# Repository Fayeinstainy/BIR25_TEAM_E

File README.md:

# Smart Swarmica - A Swarm Ant Robots Project
## Overview
This project is part of a biologically-inspired swarm robot system, where multiple robots cooperate to perform tasks such as locating a wireless charger and coordinating actions using IR signals.
All circuities were **initially developed and tested on a Raspberry Pi Pico**, and later **finalized on a custom PCB using RP2035 microcontroller chip** for integration into the final robot design.
The video for the whole development process and final demonstration can be found via this link: https://www.youtube.com/watch?v=agExd-AKbOk 

## Hardware Component 

- **IR LED**: IR333
- **IR Receiver**: TSOP38238
- **Microcontroller**: RP2350-based Raspberry Pi Pico 2W
  
- **Other**: Resistors, Transistors (for LED driving), 38kHz signal source (via PWM)

## System Architecture

## Power System Architecture (Normal Operation Mode)

## Software Architecture

## Motor Control
## Navigation
## Infrared Communication
- Uses **modulated IR signals** at 38kHz for one-way signaling between robots.
- Encodes simple messages (e.g. "Relative location is (4, 12)", "Stop Moving").
- Receiver uses TSOP382 to detect incoming signals reliably even in ambient light.

### How it works:
1. IR LED emits 38kHz modulated pulses.
2. TSOP382 detects signal and triggers logic in firmware.
3. Signal interpreted as communication or wall proximity.

## PCB Design
Designed using kiCAD 9.0, project files, schematic and PCB pdfs under bio_robots/ folder, featuring the following features:
- Populated: Common anode RGB LED, 3-pairs of IR transmitters and receivers, full bridge rectifier, parallel chargers for the supercapacitors, OR controller.
- Unpopulated: ICM-20948, 1.8V regulator, level shifters, bypass strategy (U12, D10-D13)

## Obstacle Avoidance
- Based on detecting reflection of IR signal from nearby obstacles.
- If TSOP382 receives the robot’s own IR pulses reflected from a wall, it triggers a "wall detected" event.
##  WI-FI Programming Mode

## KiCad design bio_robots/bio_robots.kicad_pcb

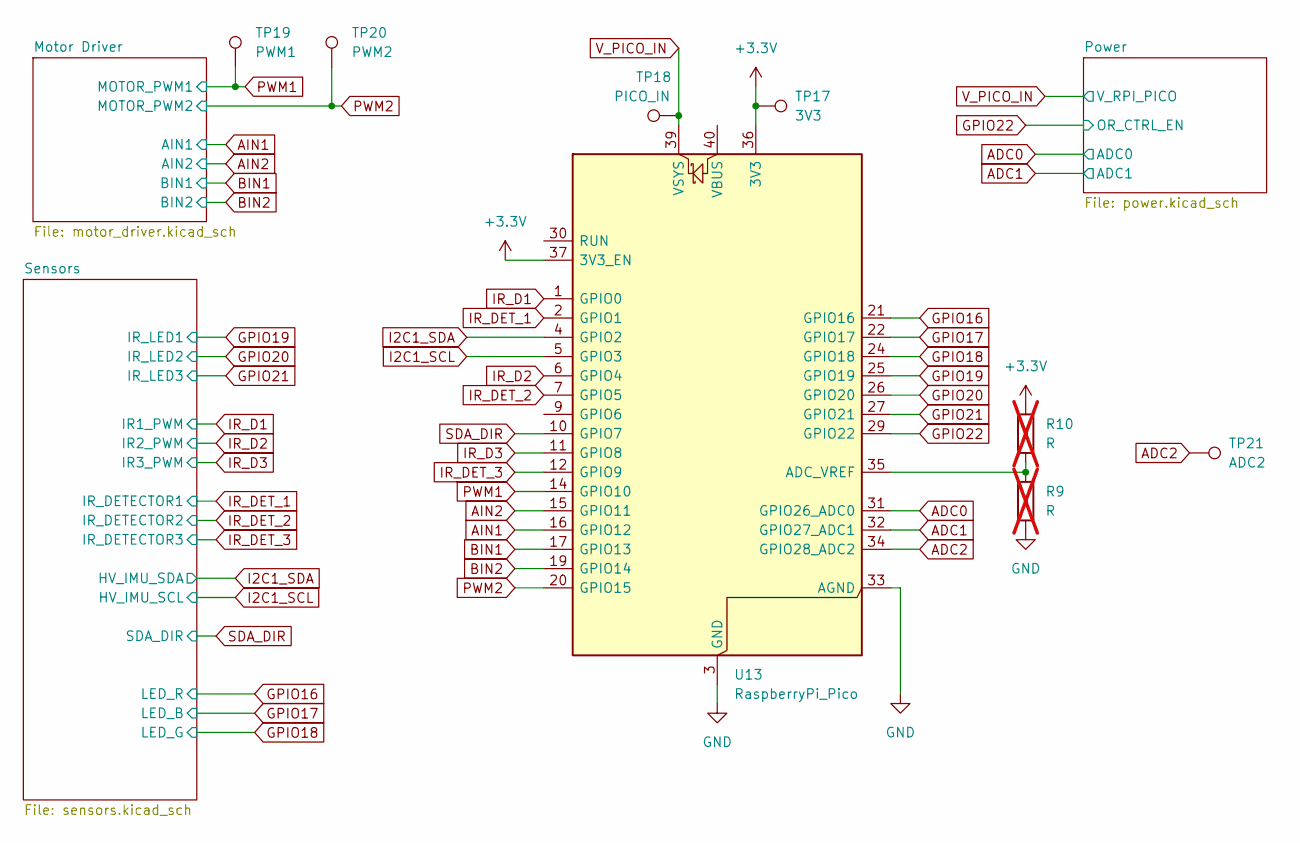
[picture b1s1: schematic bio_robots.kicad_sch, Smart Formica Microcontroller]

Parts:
R9, R10: R; R_0603_1608Metric_Pad0.98x0.95mm_HandSolder; not fitted
TP17: 3V3; TestPoint_Pad_D1.0mm
TP18: PICO_IN; TestPoint_Pad_D1.0mm
TP19: PWM1; TestPoint_Pad_D1.0mm
TP20: PWM2; TestPoint_Pad_D1.0mm
TP21: ADC2; TestPoint_Pad_D1.0mm
U13: RaspberryPi_Pico; mod_RaspberryPi_Pico_Common_THT

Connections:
ADC0: U13.31 (GPIO26_ADC0); also elsewhere on the board
ADC1: U13.32 (GPIO27_ADC1); also elsewhere on the board
ADC2: TP21.1, U13.34 (GPIO28_ADC2)
AIN1: U13.16 (GPIO12); also elsewhere on the board
AIN2: U13.15 (GPIO11); also elsewhere on the board
BIN1: U13.17 (GPIO13); also elsewhere on the board
BIN2: U13.19 (GPIO14); also elsewhere on the board
GND: R9.2, U13.3 (GND), U13.8 (GND), U13.13 (GND), U13.18 (GND), U13.23 (GND), U13.28 (GND), U13.33 (AGND), U13.38 (GND); also elsewhere on the board
GPIO16: U13.21 (GPIO16); also elsewhere on the board
GPIO17: U13.22 (GPIO17); also elsewhere on the board
GPIO18: U13.24 (GPIO18); also elsewhere on the board
GPIO19: U13.25 (GPIO19); also elsewhere on the board
GPIO20: U13.26 (GPIO20); also elsewhere on the board
GPIO21: U13.27 (GPIO21); also elsewhere on the board
GPIO22: U13.29 (GPIO22); also elsewhere on the board
I2C1_SCL: U13.5 (GPIO3); also elsewhere on the board
I2C1_SDA: U13.4 (GPIO2); also elsewhere on the board
IR_D1: U13.1 (GPIO0); also elsewhere on the board
IR_D2: U13.6 (GPIO4); also elsewhere on the board
IR_D3: U13.11 (GPIO8); also elsewhere on the board
IR_DET_1: U13.2 (GPIO1); also elsewhere on the board
IR_DET_2: U13.7 (GPIO5); also elsewhere on the board
IR_DET_3: U13.12 (GPIO9); also elsewhere on the board
unnamed: R9.1, R10.2, U13.35 (ADC_VREF)
PWM1: TP19.1, U13.14 (GPIO10); also elsewhere on the board
PWM2: TP20.1, U13.20 (GPIO15); also elsewhere on the board
SDA_DIR: U13.10 (GPIO7); also elsewhere on the board

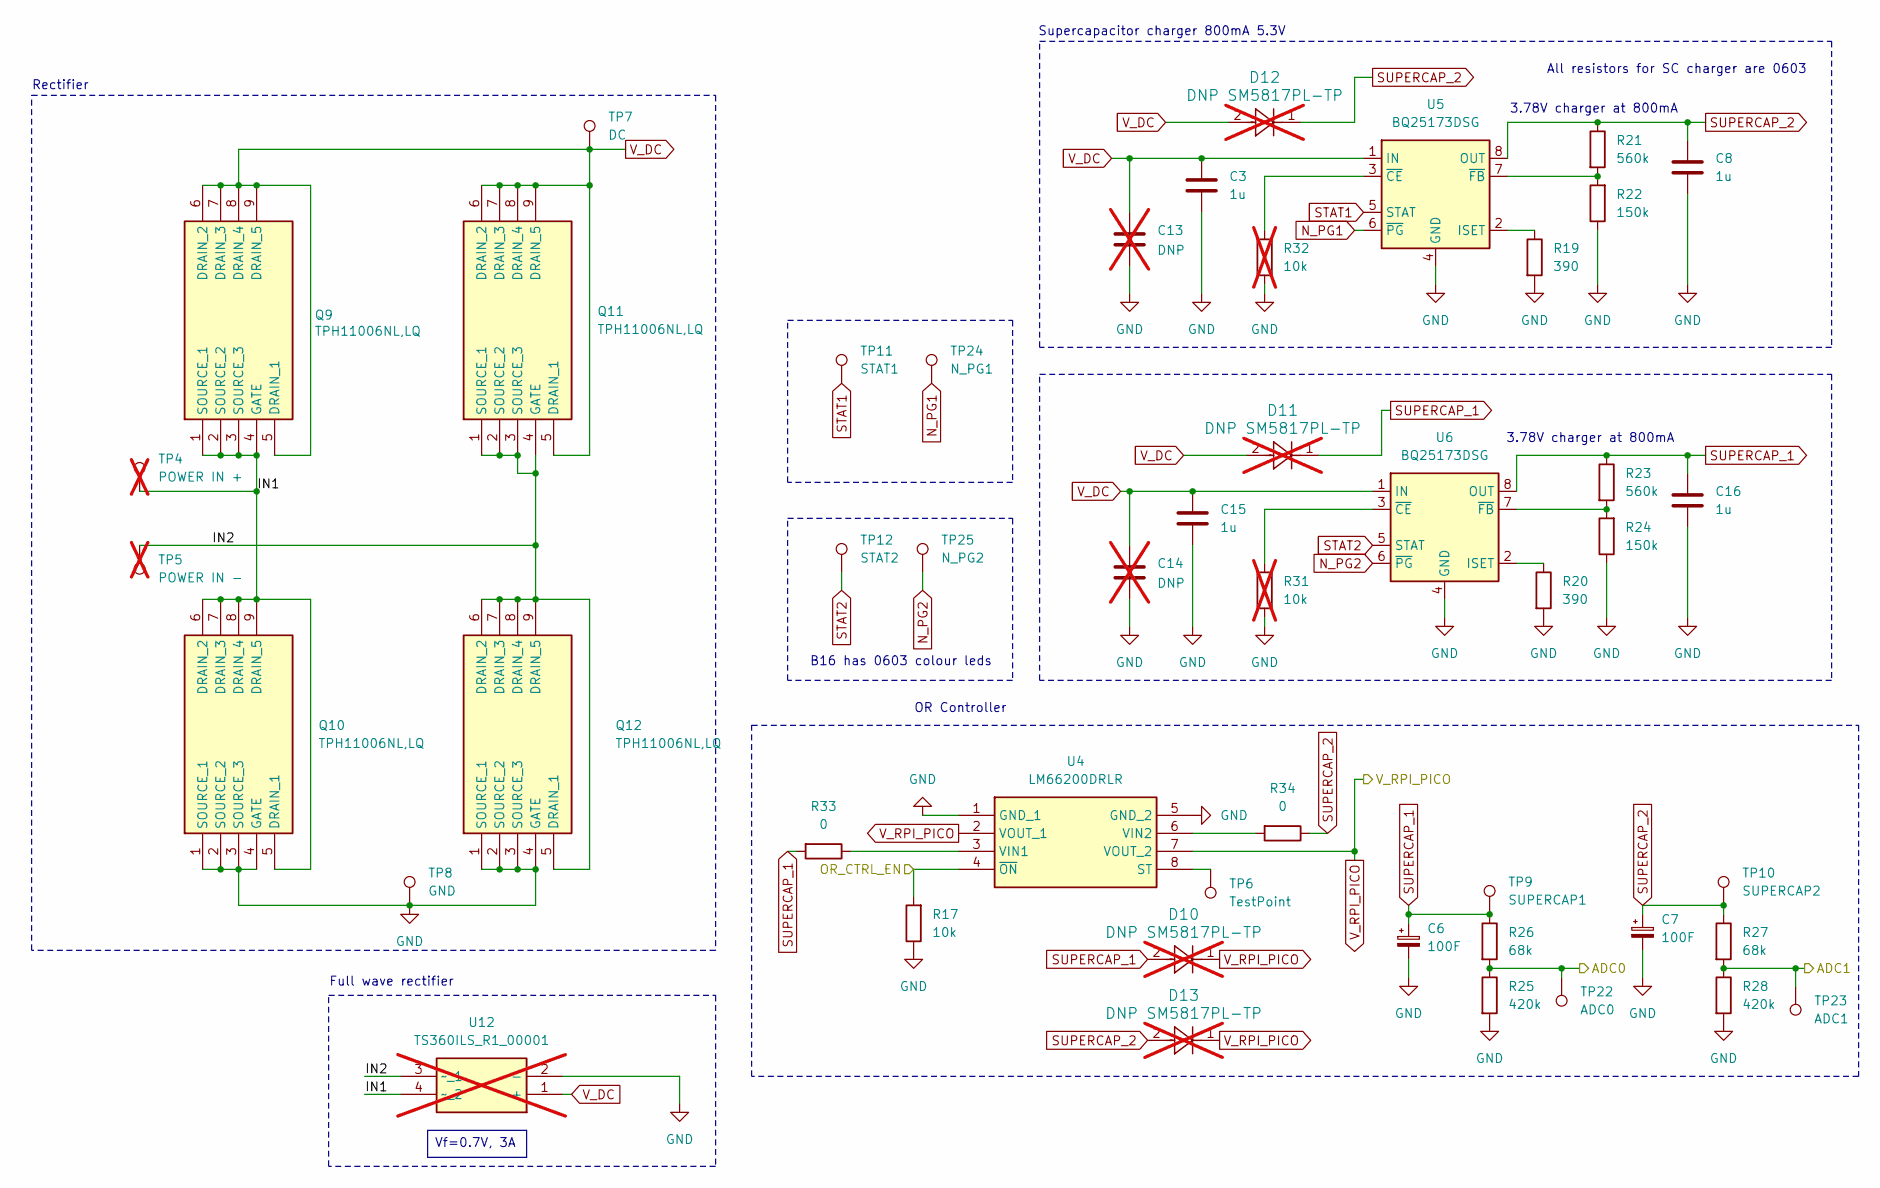
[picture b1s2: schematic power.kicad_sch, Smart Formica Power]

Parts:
C3, C8, C15, C16: 1u; C_0402_1005Metric_Pad0.74x0.62mm_HandSolder
C6, C7: 100F; 100f_CPhorizontal_Radial_D10.0mm_P5.00mm
C13, C14: DNP; C_0603_1608Metric_Pad1.08x0.95mm_HandSolder; not fitted
D10, D11, D12, D13: DNP SM5817PL-TP; CR_5817PL-TP_MCC-M; not fitted
Q9, Q10, Q11, Q12: TPH11006NL,LQ; TPH11006NLLQ; Mouser Part Number 757-TPH11006NLLQ
R17: 10k; R_0402_1005Metric_Pad0.72x0.64mm_HandSolder
R19, R20: 390; R_0402_1005Metric_Pad0.72x0.64mm_HandSolder
R21, R23: 560k; R_0603_1608Metric_Pad0.98x0.95mm_HandSolder
R22, R24: 150k; R_0603_1608Metric_Pad0.98x0.95mm_HandSolder
R25, R28: 420k; R_0603_1608Metric_Pad0.98x0.95mm_HandSolder
R26, R27: 68k; R_0603_1608Metric_Pad0.98x0.95mm_HandSolder
R31, R32: 10k; R_0402_1005Metric_Pad0.72x0.64mm_HandSolder; not fitted
R33, R34: 0; R_0603_1608Metric_Pad0.98x0.95mm_HandSolder
TP4: POWER IN +; TestPoint_Bridge_Pitch5.08mm_Drill1.3mm; not fitted
TP5: POWER IN -; TestPoint_Bridge_Pitch5.08mm_Drill1.3mm; not fitted
TP6: TestPoint; TestPoint_Pad_D1.0mm
TP7: DC; TestPoint_Pad_D1.0mm
TP8: GND; TestPoint_Pad_D1.0mm
TP9: SUPERCAP1; TestPoint_Pad_D1.0mm
TP10: SUPERCAP2; TestPoint_Pad_D1.0mm
TP11: STAT1; TestPoint_Pad_D1.0mm
TP12: STAT2; TestPoint_Pad_D1.0mm
TP22: ADC0; TestPoint_Pad_D1.0mm
TP23: ADC1; TestPoint_Pad_D1.0mm
TP24: N_PG1; TestPoint_Pad_D1.0mm
TP25: N_PG2; TestPoint_Pad_D1.0mm
U4: LM66200DRLR; SOTFL50P160X60-8N; Mouser Part Number 595-LM66200DRLR
U5, U6: BQ25173DSG; WSON-8-1EP_2x2mm_P0.5mm_EP0.9x1.6mm
U12: TS360ILS_R1_00001; SOP400P650X145-4N; Mouser Part Number 241-TS360ILSR100001; not fitted

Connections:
/Power/IN1: Q9.1 (SOURCE_1), Q9.2 (SOURCE_2), Q9.3 (SOURCE_3), Q9.4 (GATE), Q10.5 (DRAIN_1), Q10.6 (DRAIN_2), Q10.7 (DRAIN_3), Q10.8 (DRAIN_4), Q10.9 (DRAIN_5), TP4.1, U12.4 (~_2)
/Power/IN2: Q11.1 (SOURCE_1), Q11.2 (SOURCE_2), Q11.3 (SOURCE_3), Q11.4 (GATE), Q12.5 (DRAIN_1), Q12.6 (DRAIN_2), Q12.7 (DRAIN_3), Q12.8 (DRAIN_4), Q12.9 (DRAIN_5), TP5.1, U12.3 (~_1)
ADC0: R25.1, R26.2, TP22.1; also elsewhere on the board
ADC1: R27.2, R28.1, TP23.1; also elsewhere on the board
GND: C3.2, C6.2, C7.2, C8.2, C13.2, C14.2, C15.2, C16.2, Q10.1 (SOURCE_1), Q10.2 (SOURCE_2), Q10.3 (SOURCE_3), Q10.4 (GATE), Q12.1 (SOURCE_1), Q12.2 (SOURCE_2), Q12.3 (SOURCE_3), Q12.4 (GATE), R17.1, R19.2, R20.2, R22.1, R24.1, R25.2, R28.2, R31.1, R32.1, TP8.1, U4.1 (GND_1), U4.5 (GND_2), U5.4 (GND), U5.9 (GND), U6.4 (GND), U6.9 (GND), U12.2 (-); also elsewhere on the board
GPIO22: R17.2, U4.4 (~ON); also elsewhere on the board
N_PG1: TP24.1, U5.6 (~PG)
N_PG2: TP25.1, U6.6 (~PG)
unnamed: TP6.1, U4.8 (ST)
unnamed: R33.1, U4.3 (VIN1)
unnamed: R34.2, U4.6 (VIN2)
unnamed: R19.1, U5.2 (ISET)
unnamed: R32.2, U5.3 (~CE)
unnamed: R21.2, R22.2, U5.7 (~FB)
unnamed: R20.1, U6.2 (ISET)
unnamed: R31.2, U6.3 (~CE)
unnamed: R23.2, R24.2, U6.7 (~FB)
STAT1: TP11.1, U5.5 (STAT)
STAT2: TP12.1, U6.5 (STAT)
SUPERCAP_1: C6.1, C16.1, D10.2, D11.1, R23.1, R26.1, R33.2, TP9.1, U6.8 (OUT)
SUPERCAP_2: C7.1, C8.1, D12.1, D13.2, R21.1, R27.1, R34.1, TP10.1, U5.8 (OUT)
V_DC: C3.1, C13.1, C14.1, C15.1, D11.2, D12.2, Q9.5 (DRAIN_1), Q9.6 (DRAIN_2), Q9.7 (DRAIN_3), Q9.8 (DRAIN_4), Q9.9 (DRAIN_5), Q11.5 (DRAIN_1), Q11.6 (DRAIN_2), Q11.7 (DRAIN_3), Q11.8 (DRAIN_4), Q11.9 (DRAIN_5), TP7.1, U5.1 (IN), U6.1 (IN), U12.1 (+)

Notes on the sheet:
Rectifier
3.78V charger at 800mA
Supercapacitor charger 800mA 5.3V
OR Controller
All resistors for SC charger are 0603
B16 has 0603 colour leds
Full wave rectifier
Vf=0.7V, 3A

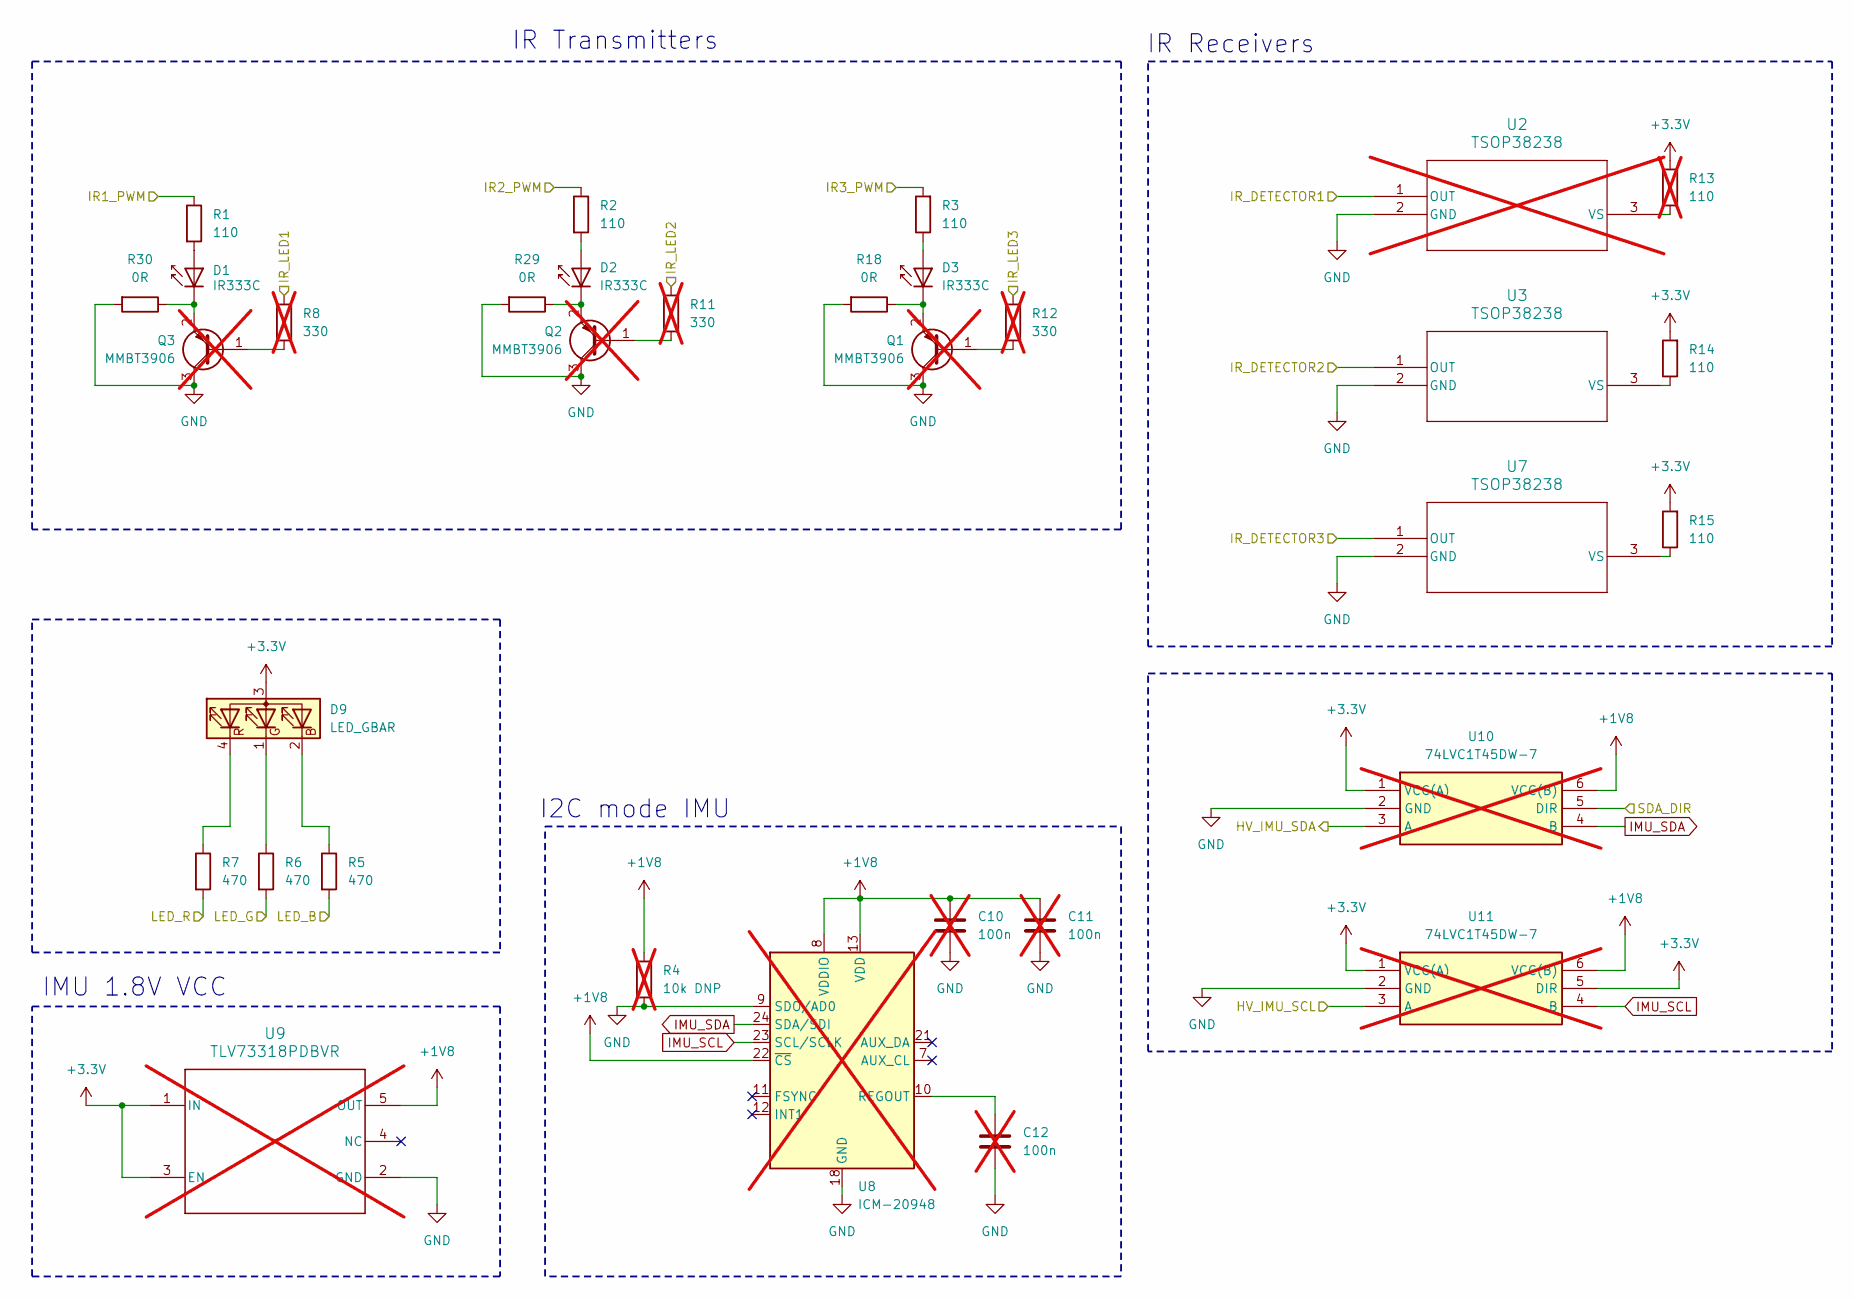
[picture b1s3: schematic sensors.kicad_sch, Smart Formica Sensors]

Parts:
C10, C11, C12: 100n; C_0402_1005Metric_Pad0.74x0.62mm_HandSolder; not fitted
D1, D2, D3: IR333C; LED_D5.0mm_IRGrey
D9: LED_GBAR; LED_D5.0mm-4_RGB_Wide_Pins
Q1, Q2, Q3: MMBT3906; SOT-23; not fitted
R1, R2, R3, R14, R15: 110; R_0603_1608Metric_Pad0.98x0.95mm_HandSolder
R4: 10k DNP; R_0402_1005Metric_Pad0.72x0.64mm_HandSolder; not fitted
R5, R6, R7: 470; R_0603_1608Metric_Pad0.98x0.95mm_HandSolder
R8, R11, R12: 330; R_0603_1608Metric_Pad0.98x0.95mm_HandSolder; not fitted
R13: 110; R_0603_1608Metric_Pad0.98x0.95mm_HandSolder; not fitted
R18, R29, R30: 0R; R_0603_1608Metric_Pad0.98x0.95mm_HandSolder
U2: TSOP38238; not fitted
U3, U7: TSOP38238
U8: ICM-20948; InvenSense_QFN-24_3x3mm_P0.4mm; not fitted
U9: TLV73318PDBVR; DBV0005A_N; not fitted
U10, U11: 74LVC1T45DW-7; SOT65P210X110-6N; Mouser Part Number 621-74LVC1T45DW-7; not fitted

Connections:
+1V8: C10.1, C11.1, R4.1, U8.8 (VDDIO), U8.13 (VDD), U8.22 (~CS), U9.5 (OUT), U10.6 (VCC(B)), U11.6 (VCC(B))
GND: C10.2, C11.2, C12.2, Q1.3 (C), Q2.3 (C), Q3.3 (C), R4.2, R18.2, R29.2, R30.2, U2.2 (GND), U3.2 (GND), U7.2 (GND), U8.9 (SDO/AD0), U8.18 (GND), U8.20 (GND), U9.2 (GND), U10.2 (GND), U11.2 (GND); also elsewhere on the board
GPIO16: R7.2; also elsewhere on the board
GPIO17: R5.2; also elsewhere on the board
GPIO18: R6.2; also elsewhere on the board
GPIO19: R8.1; also elsewhere on the board
GPIO20: R11.1; also elsewhere on the board
GPIO21: R12.1; also elsewhere on the board
I2C1_SCL: U11.3 (A); also elsewhere on the board
I2C1_SDA: U10.3 (A); also elsewhere on the board
IMU_SCL: U8.23 (SCL/SCLK), U11.4 (B)
IMU_SDA: U8.24 (SDA/SDI), U10.4 (B)
IR_D1: R1.1; also elsewhere on the board
IR_D2: R2.1; also elsewhere on the board
IR_D3: R3.2; also elsewhere on the board
IR_DET_1: U2.1 (OUT); also elsewhere on the board
IR_DET_2: U3.1 (OUT); also elsewhere on the board
IR_DET_3: U7.1 (OUT); also elsewhere on the board
unnamed: D1.2 (A), R1.2
unnamed: D1.1 (K), Q3.2 (E), R30.1
unnamed: D2.2 (A), R2.2
unnamed: D2.1 (K), Q2.2 (E), R29.1
unnamed: D3.2 (A), R3.1
unnamed: D3.1 (K), Q1.2 (E), R18.1
unnamed: D9.2 (BK), R5.1
unnamed: D9.1 (GK), R6.1
unnamed: D9.4 (RK), R7.1
unnamed: Q1.1 (B), R12.2
unnamed: Q2.1 (B), R11.2
unnamed: Q3.1 (B), R8.2
unnamed: R13.1, U2.3 (VS)
unnamed: R14.1, U3.3 (VS)
unnamed: R15.1, U7.3 (VS)
unnamed: C12.1, U8.10 (REGOUT)
SDA_DIR: U10.5 (DIR); also elsewhere on the board

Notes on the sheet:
IR Receivers
IR Transmitters
I2C mode IMU
IMU 1.8V VCC

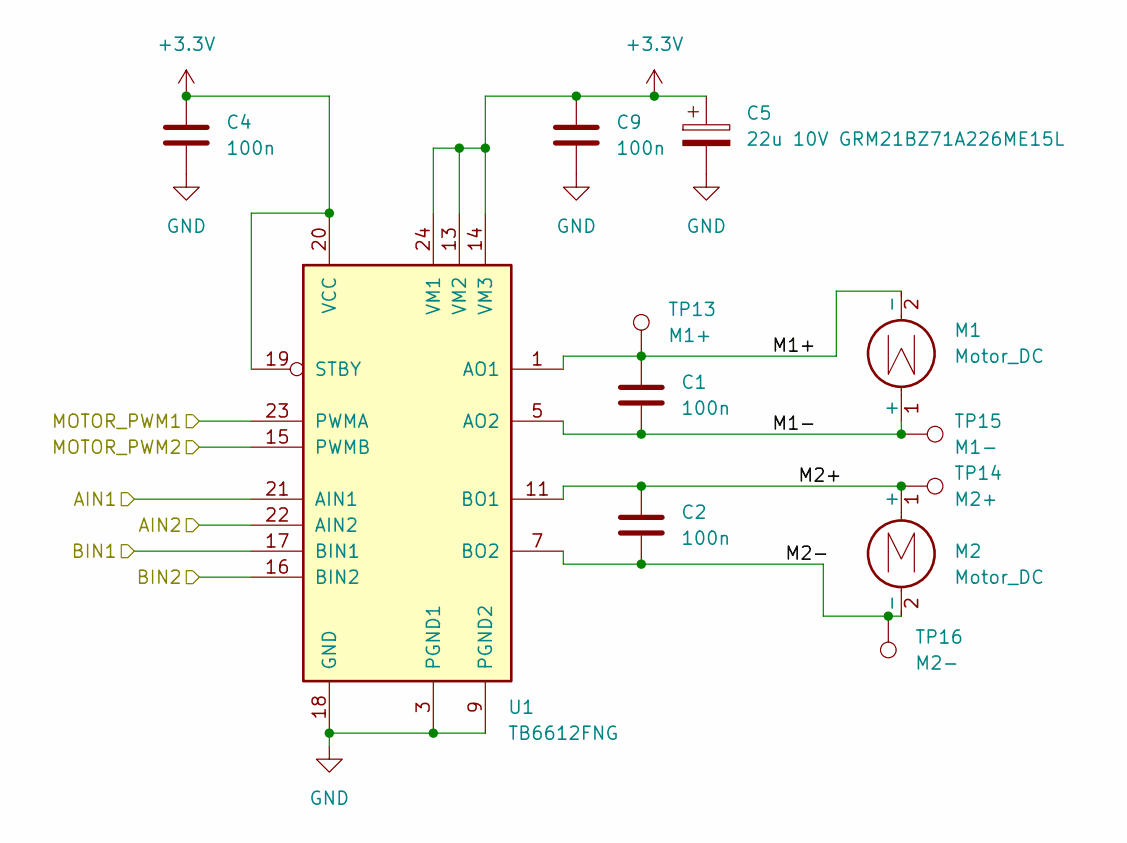
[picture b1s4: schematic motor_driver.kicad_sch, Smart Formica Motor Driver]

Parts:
C1, C2, C4, C9: 100n; C_0603_1608Metric_Pad1.08x0.95mm_HandSolder
C5: 22u 10V GRM21BZ71A226ME15L; C_0805_2012Metric_Pad1.18x1.45mm_HandSolder
M1, M2: Motor_DC; mod_motor_v2_VZ6SC0B0060081
TP13: M1+; TestPoint_Pad_D1.0mm
TP14: M2+; TestPoint_Pad_D1.0mm
TP15: M1-; TestPoint_Pad_D1.0mm
TP16: M2-; TestPoint_Pad_D1.0mm
U1: TB6612FNG; SSOP-24_5.3x8.2mm_P0.65mm

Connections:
/Motor Driver/M1+: C1.1, M1.2 (-), TP13.1, U1.1 (AO1), U1.2 (AO1)
/Motor Driver/M1-: C1.2, M1.1 (+), TP15.1, U1.5 (AO2), U1.6 (AO2)
/Motor Driver/M2+: C2.1, M2.1 (+), TP14.1, U1.11 (BO1), U1.12 (BO1)
/Motor Driver/M2-: C2.2, M2.2 (-), TP16.1, U1.7 (BO2), U1.8 (BO2)
AIN1: U1.21 (AIN1); also elsewhere on the board
AIN2: U1.22 (AIN2); also elsewhere on the board
BIN1: U1.17 (BIN1); also elsewhere on the board
BIN2: U1.16 (BIN2); also elsewhere on the board
GND: C4.2, C5.2, C9.2, U1.3 (PGND1), U1.4 (PGND1), U1.9 (PGND2), U1.10 (PGND2), U1.18 (GND); also elsewhere on the board
PWM1: U1.23 (PWMA); also elsewhere on the board
PWM2: U1.15 (PWMB); also elsewhere on the board

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
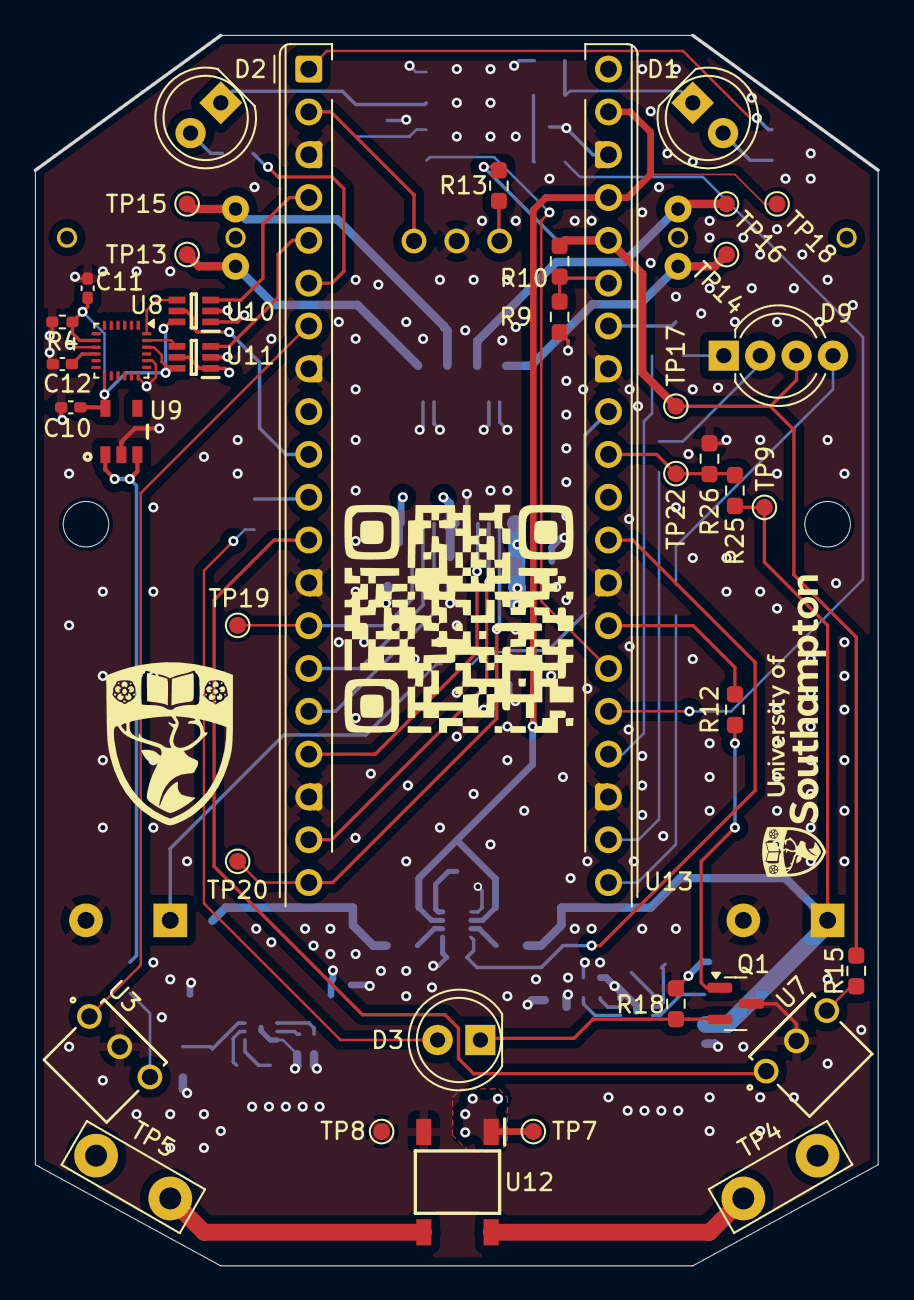
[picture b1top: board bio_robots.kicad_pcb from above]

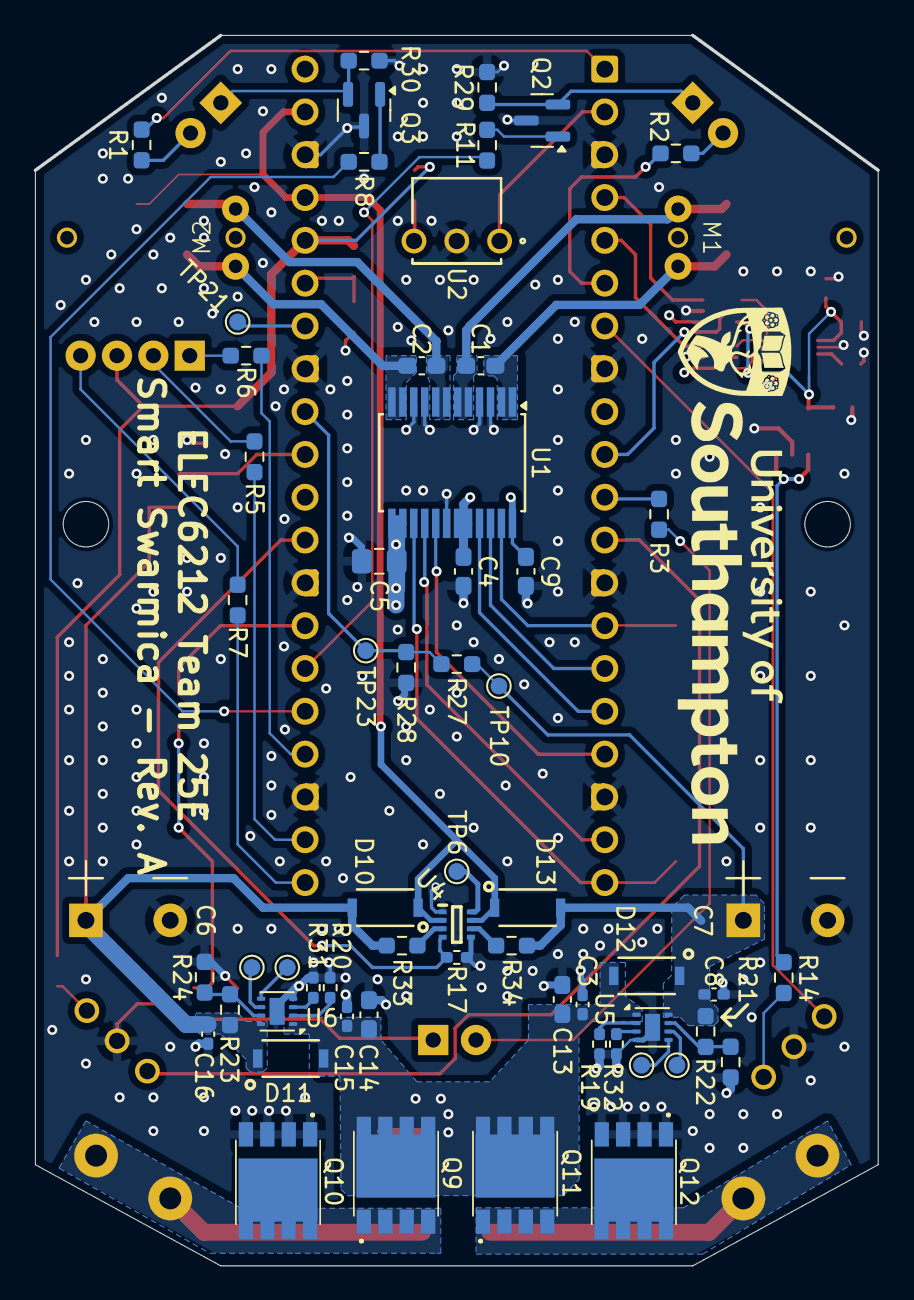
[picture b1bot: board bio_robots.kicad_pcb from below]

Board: 4 copper layers, 50.0 x 72.9 mm, 103 parts (62 on the bottom side), 70 nets.

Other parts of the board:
MH1, MH2: MountingHole_2.7mm_M2.5_DIN965

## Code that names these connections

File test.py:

from picozero import RGBLED
from time import sleep
import math
import random
from machine import Pin , PWM
import machine
import rp2
import sys
rgb = RGBLED(red = 16, green = 17, blue = 18,active_high=False) 
distance = 1.0 #polar distancce of the current location
angle = 0.0 #polar angle of the current location
direction = 0.0 #where the robot is facing
coord = [distance,angle, direction] 
turn_left = 0
turn_right = 0
turn = [turn_left, turn_right] 
count = 0
led = Pin('LED', Pin.OUT)

ain1 = Pin(12,Pin.OUT)
ain2 = Pin(11, Pin.OUT)
bin1 = Pin(13,Pin.OUT)
bin2 = Pin(14,Pin.OUT)
pwma = PWM(Pin(10))
pwmb = PWM(Pin(15))
pwma.freq(24000)
pwmb.freq(24000)

def RotateCW(duty, pwm):
    ain1.value(1)
    ain2.value(0)
    bin1.value(1)
    bin2.value(0)
    duty_16 = int(duty)
    pwm.duty_u16(duty_16)

def RotateCCW(duty, pwm):
    ain1.value(0)
    ain2.value(1)
    bin1.value(0)
    bin2.value(1)
    duty_16 = int(duty)
    pwm.duty_u16(duty_16)
    led.toggle()
    
def StopMotor():
    ain1.value(0)
    ain2.value(0)
    bin1.value(0)
    bin2.value(0)
    pwma.duty_u16(0)
    pwmb.duty_u16(0)
    led.toggle()
    
def forward(duty):
    x = coord[0]*math.cos(coord[1]) + math.cos(coord[2])
    y = coord[0]*math.sin(coord[1]) + math.sin(coord[2])
    coord[0] = math.sqrt(x**2 + y**2)
    coord[1] = math.atan2(y,x)
    RotateCW(duty, pwma)
    RotateCW(duty, pwmb)
    rgb.color = (255, 0, 0) #red

    return coord,turn

def left(duty):
    coord[2] += math.pi/2
    coord[2] = (coord[2] + math.pi) % (2 * math.pi) - math.pi  # Keep within [-π, π]

    x = coord[0]*math.cos(coord[1]) + math.cos(coord[2])
    y = coord[0]*math.sin(coord[1]) + math.sin(coord[2])
    coord[0] = math.sqrt(x**2 + y**2)
    coord[1] = math.atan2(y,x)
    turn[0] +=1
    rgb.color = (0, 255, 0) #green
    RotateCW(duty, pwma)
    RotateCCW(duty, pwmb)
    return coord,turn

def right(duty):
    coord[2] -= math.pi/2
    coord[2] = (coord[2] + math.pi) % (2 * math.pi) - math.pi  # Keep within [-π, π]

    x = coord[0]*math.cos(coord[1]) + math.cos(coord[2])
    y = coord[0]*math.sin(coord[1]) + math.sin(coord[2])
    coord[0] = math.sqrt(x**2 + y**2)
    coord[1] = math.atan2(y,x)
    turn[1] += 1
    rgb.color = (0, 0, 255) #blue
    RotateCCW(duty, pwma)
    RotateCW(duty, pwmb)
    return coord,turn

def backward(duty):
    x = coord[0]*math.cos(coord[1]) - math.cos(coord[2])
    y = coord[0]*math.sin(coord[1]) - math.sin(coord[2])
    coord[0] = math.sqrt(x**2 + y**2)
    coord[1] = math.atan2(y,x)
    rgb.color = (255, 128, 0) #orange
    RotateCCW(duty, pwma)
    RotateCCW(duty, pwmb)

    return coord,turn

def foraging():
    '''Randomly move to find a charger'''
    count = 0
    while (math.fabs(coord[0]*math.cos(coord[1]) - station[0]*math.cos(station[1])) > 2 or math.fabs(coord[0]*math.sin(coord[1]) - station[0]*math.sin(station[1])) > 2)  and count < 30:
        random.choice(movement)(48000)
        sleep(3)
        print(coord,turn)
        count +=1
        rgb.color= (0,0,0)
        sleep(1)
        #if math.fabs(coord[0] - station[0]) < 1 and math.cos(coord[1]) * math.cos(station[1]) > 0 and math.sin(coord[1]) * math.sin(station[1]) > 0:
           # print('Gettng there')   these are for debugging purpose 
    return coord
#stop and talk to each other
def get_charge(destination):
    """Navigates the robot to the charger"""
    count = 0
    while math.fabs(coord[0]*math.sin(coord[1]) - destination[1]) > 0.9 and count < 100 :
        if  coord[0]*math.sin(coord[1]) <= destination[1] : # Robot needs to move up
            if not (math.pi/2 -0.2 < coord[2] < math.pi/2 +0.2):
                left()
                sleep(0.5)
            else:
                forward()
                sleep(0.5)
        else: #robot needs to move down
            if not ( -math.pi/2 - 0.2 <coord[2] < -math.pi/2 + 0.2):  # Check if robot is facing down
                right()  # Turn right to face downward
                sleep(0.5)
            else:
                forward()  # Move forward
                sleep(0.5)
        print(coord[0]*math.sin(coord[1]))
        count +=1
    while math.fabs(coord[0]*math.cos(coord[1]) - destination[0]) > 0.9 and count < 100 :
        if  coord[0]*math.cos(coord[1]) > destination[0]: # Move to the left
            if (-math.pi/2-0.000001 <= coord[2] <= math.pi/2):  # Check if robot is facing left
                left()  # Turn left to face right
                sleep(0.5)
            else:
                forward()  # Move forward
                sleep(0.5)
        else:  # Need to go towards positive X direction
            if not (-0.2 <coord[2] < 0.2) :  # Check if robot is facing right
                right()  # Turn right to face left
                sleep(0.5)
            else:
                forward()  # Move forward
                sleep(0.5)
        print(coord[0]*math.cos(coord[1]))
        count +=1
    print(coord)
    return coord
    
'''Unconment only what you want it to do '''
station = [8,1] # artificially set station position
movement  = [forward,left,right]
nest = [0,0] #coordinate of the nest


#foraging()
#get_charge([station[0]*math.cos(station[1]),station[0]*math.sin(station[1])])
#get_charge(nest) #go home


        
#rgb.color = (0, 0,255 ) #red
# sleep(2)
# rgb.color = (0, 255, 0) #green
# sleep(2)
# rgb.color = (0,0,255) #blue

left(24000)  # Move forward
sleep(5)
StopMotor()

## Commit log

2025-03-24 Add a file containing navigation algorithms
    Incomplete version still requires
    - obstacle avoidant
    - update position
    - broadcasting position
    - imu implementation for finer movement
2025-04-22 Add files via upload
    1. Includes IR comms between Rx and Tx separately which can be improved to switch between Rx and Tx.
    2. Decoding is not robust enough. will be improved.
    3. Includes obstacle avoidance algorithm.
    4. Needs to be merged with navigation algorithm and motor controller.
2025-04-22 Create README.md
    Skeleton draft.
2025-04-30 Update test.py
    Change GPIO pins according to the robot PCB.
    Still need to integrate IR and Wall collision.
2025-05-07 Update Rx.py
    Rx not detecting same bits
2025-05-09 Update README.md
    add a software architecture flow chart
2025-05-11 ADC and OR controller driver
    Disables output to the OR controller through its active low input when either of the two supercapacitors reaches a voltage lower than 2.4V
2025-05-11 Rev. A PCB-robot kiCAD files
    Originated in kiCAD 9.0, with generated gerber ffiles, schematic and PCB pdfs
2025-05-15 Update and rename test.py to main.py
    Final working version, without WIFI though
2025-05-15 Update main.py
    Delete ain/bin in. StopMotor()
    Change reset() to sys.exit() for soft reboot instead of hard reboot
2025-05-17 Add the final demo video. Update README.md
    final video demo: https://www.youtube.com/watch?v=agExd-AKbOk
